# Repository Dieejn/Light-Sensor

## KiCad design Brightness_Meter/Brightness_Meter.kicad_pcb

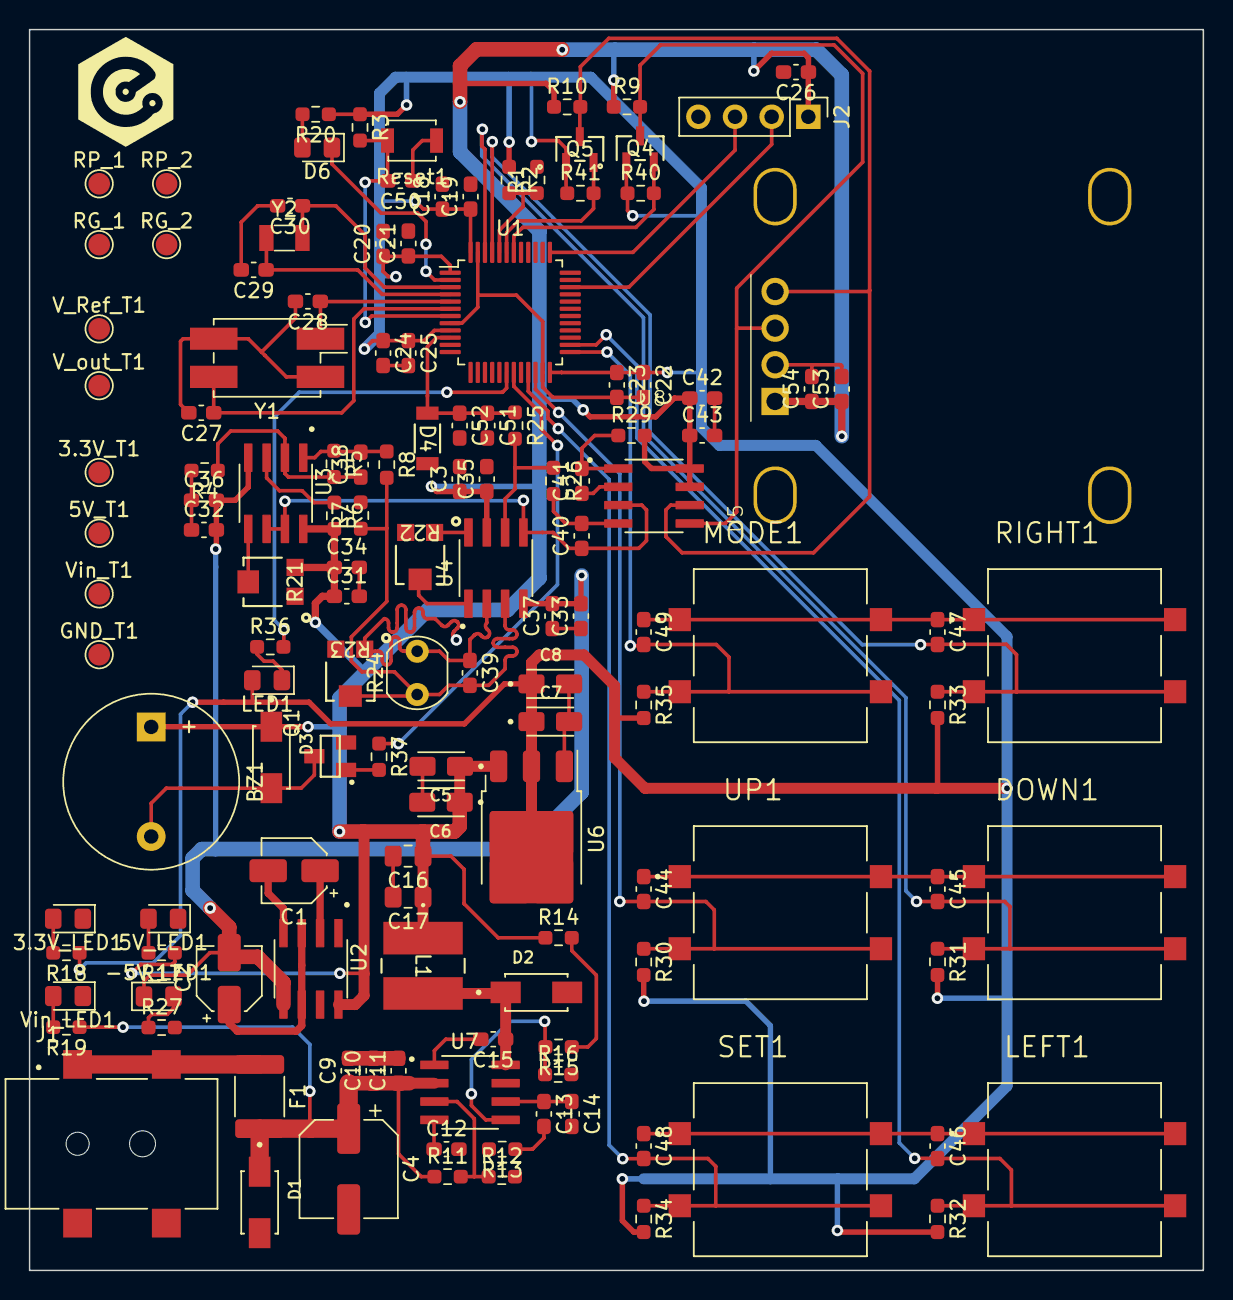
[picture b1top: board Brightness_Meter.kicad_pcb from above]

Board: 2 copper layers, 81.4 x 86.0 mm, 137 parts (0 on the bottom side), 57 nets.

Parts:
3.3V_LED1, 5V_LED1: BLUE; LED_0805_2012Metric_Pad1.15x1.40mm_HandSolder
3.3V_T1: 3.3V; TestPoint_Pad_D1.5mm
5V_T1: 5V; TestPoint_Pad_D1.5mm
-5V_LED1: BLUE; LED_0805_2012Metric_Pad1.15x1.40mm_HandSolder
BZ1: Buzzer; Buzzer_12x9.5RM7.6
C1, C2: 10uF/16V; CP_Elec_4x5.4
C3, C26, C31, C32, C33, C42, C51, C53: 10uF/16V; C_0603_1608Metric_Pad1.08x0.95mm_HandSolder
C4: 22uF/25V; CP_Elec_6.3x5.4
C5, C8: 1uF/25V; CAPMP3216X180N
C6, C7: 10uF/16V; CAPMP3216X180N
C9, C10: 4.7uF/25V; C_0603_1608Metric_Pad1.08x0.95mm_HandSolder
C11, C12, C25: 10nF/50V; C_0603_1608Metric_Pad1.08x0.95mm_HandSolder
C13: 1nF/50V; C_0603_1608Metric_Pad1.08x0.95mm_HandSolder
C14: 47pF/50V; C_0603_1608Metric_Pad1.08x0.95mm_HandSolder
C15: 0.1uF/16V; C_0603_1608Metric_Pad1.08x0.95mm_HandSolder
C16, C17: 47uF/6.3V; C_0805_2012Metric_Pad1.18x1.45mm_HandSolder
C18, C20, C22: 4.7uF/10V; C_0603_1608Metric_Pad1.08x0.95mm_HandSolder
C19, C21, C23, C34, C35, C36, C37, C40, C41, C43, C44, C45, C46, C47, C48, C49, C50, C52, C54: 100nF/16V; C_0603_1608Metric_Pad1.08x0.95mm_HandSolder
C24, C39: 1uF/16V; C_0603_1608Metric_Pad1.08x0.95mm_HandSolder
C27, C28, C29, C30: 20pF/50V; C_0603_1608Metric_Pad1.08x0.95mm_HandSolder
C38: 10pF/50V; C_0603_1608Metric_Pad1.08x0.95mm_HandSolder
D1, D2, D3: SS34; DIOM4325X250N
D4: ZMM3V3; ZDO_ZMM_3p5x1p45_STM
D6: Led_test; LED_0805_2012Metric_Pad1.15x1.40mm_HandSolder
DOWN1: DOWN; SW_TL3300CF260Q
F1: Fuse_Small; Fuse_1812_4532Metric_Pad1.30x3.40mm_HandSolder
GND_T1: GND; TestPoint_Pad_D1.5mm
J1: JACK-DC; SPARKFUN_PRT-12748
J2: Load Program; PinHeader_1x04_P2.54mm_Vertical
L1: 6.8uH/2.2A; IND_SDE0604A_5P8X5P2X4P5_BRN
LED1: RED; LED_0805_2012Metric_Pad1.15x1.40mm_HandSolder
LEFT1: LEFT; SW_TL3300CF260Q
MODE1: MODE; SW_TL3300CF260Q
Q1: MMBT2222A; SOT23
Q4, Q5: BSN20; SOT23_NEX
R1, R2, R25, R26: 0/1%; R_0603_1608Metric_Pad0.98x0.95mm_HandSolder
R3, R9, R10, R16, R30, R31, R32, R33, R34, R35, R40, R41: 10k/1%; R_0603_1608Metric_Pad0.98x0.95mm_HandSolder
R4, R5, R6, R7, R8: R_Small_US; R_0603_1608Metric_Pad0.98x0.95mm_HandSolder
R11: 330k/1%; R_0603_1608Metric_Pad0.98x0.95mm_HandSolder
R12: 47k/1%; R_0603_1608Metric_Pad0.98x0.95mm_HandSolder
R13: 30k/1%; R_0603_1608Metric_Pad0.98x0.95mm_HandSolder
R14: 2.49k/1%; R_0603_1608Metric_Pad0.98x0.95mm_HandSolder
R15: 49.9k/1%; R_0603_1608Metric_Pad0.98x0.95mm_HandSolder
R17, R18, R20, R36, R37: 1k/1%; R_0603_1608Metric_Pad0.98x0.95mm_HandSolder
R19, R27: 4.7k/1%; R_0603_1608Metric_Pad0.98x0.95mm_HandSolder
R21: EVM-3ESX50B14; EVM-3ESX50B14_PAN
R22, R23: EVM-3E; EVM-3ESX50B14_PAN
R24: GL5528; R_LDR_5.0x4.1mm_P3mm_Vertical
R29: 220/1%; R_0603_1608Metric_Pad0.98x0.95mm_HandSolder
RG_1, RG_2: RG; TestPoint_Pad_D1.5mm
RIGHT1: RIGHT; SW_TL3300CF260Q
RP_1, RP_2: RP; TestPoint_Pad_D1.5mm
Reset1: SW_Push; SW_SPST_B3U-1000P
SET1: SET; SW_TL3300CF260Q
U1: STM32F030C8Tx; LQFP-48_7x7mm_P0.5mm
U2: ICL7662CPA; SOIC127P600X175-8N
U3: MCP6002; SOIC127P599X173-8N
U4: INA128; SOIC127P599X175-8N
U5: SSD1306
U6: LM1117DT-3.3; TO-252-3_TabPin2
U7: TPS54331D; SOIC127P599X175-8N
U8: HX710B
UP1: UP; SW_TL3300CF260Q
V_Ref_T1: V_Ref; TestPoint_Pad_D1.5mm
V_out_T1: V_out; TestPoint_Pad_D1.5mm
Vin_LED1: BLUE; LED_0805_2012Metric_Pad1.15x1.40mm_HandSolder
Vin_T1: Vin; TestPoint_Pad_D1.5mm
Y1: 8MHz; Crystal_SMD_EuroQuartz_MQ-4Pin_7.0x5.0mm_HandSoldering
Y2: 32.768KHz; Crystal_SMD_3215-2Pin_3.2x1.5mm

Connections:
+3.3V: 3.3V_T1.1, C7.1, C8.1, C18.1, C19.1, C20.1, C21.1, C22.1, C23.1, C24.1, C25.1, LED1.2 (A), Q4.1 (G), Q5.1 (G), R2.1, R3.1, R18.1, R20.1, R30.2, R31.2, R32.2, R33.2, R34.2, R35.2, R40.1, R41.1, U1.1 (VDD), U1.9 (VDDA), U1.24 (VDD), U1.48 (VDD), U6.2 (VO)
+5V: 5V_T1.1, BZ1.1 (-), C3.1, C5.1, C6.1, C16.1, C17.1, C26.1, C31.1, C34.1, C35.1, C42.1, C43.1, C53.1, C54.1, D3.C, J2.1, L1.1, R6.2, R9.1, R10.1, R14.1, R17.1, R21.3, R29.2, U2.8 (V+), U3.8 (VDD), U4.7 (V+), U5.1 (vcc), U6.3 (VI), U8.7 (DVDD), U8.8 (AVDD)
-5V: -5V_LED1.1 (K), C2.2, C32.2, C33.2, C36.2, C37.2, U2.5 (VOUT), U3.4 (VSS), U4.4 (V-)
/MCU/BOOT0: R1.1, R2.2, U1.44 (BOOT0)
/MCU/LED_TEST: D6.1 (K), U1.2 (PC13)
/MCU/OSC32_IN: C30.1, U1.3 (PC14), Y2.1
/MCU/OSC32_OUT: C29.1, U1.4 (PC15), Y2.2
/MCU/OSC_IN: C28.1, U1.5 (PF0), Y1.1
/MCU/OSC_OUT: C27.1, U1.6 (PF1), Y1.3
/MCU/RESET: C50.2, R3.2, Reset1.2, U1.7 (NRST)
/MCU/SWCLK: J2.3, U1.37 (PA14)
/MCU/SWDIO: J2.2, U1.34 (PA13)
/Power/Vin: C4.1, C9.1, C10.1, C11.1, D1.C, F1.2, R11.1, R19.1, U7.2 (VIN), Vin_T1.1
/measure/CURRENT_SRC: C39.2, R7.1, R8.2, R23.2, R24.1, RP_1.1, U4.3 (+)
/measure/vout: R25.2, R26.1, U4.6, V_out_T1.1
ADC_HX71OB: C40.2, R26.2, U8.4 (INP)
ADC_INO: C51.1, C52.1, D4.1, R25.1, U1.10 (PA0)
BUZZER: R37.1, U1.19 (PB1)
GND: 3.3V_LED1.1 (K), 5V_LED1.1 (K), C2.1, C3.2, C4.2, C5.2, C6.2, C7.2, C8.2, C9.2, C10.2, C11.2, C12.2, C14.2, C16.2, C17.2, C18.2, C19.2, C20.2, C21.2, C22.2, C23.2, C24.2, C25.2, C26.2, C27.2, C28.2, C29.2, C30.2, C31.2, C32.1, C33.1, C34.2, C35.2, C36.1, C37.1, C39.1, C41.1, C42.2, C43.2, C44.1, C45.1, C46.1, C47.1, C48.1, C49.1, C50.1, C51.2, C52.2, C53.2, C54.2, D1.A, D2.A, D4.2, DOWN1.1, DOWN1.2, GND_T1.1, J1.2, J1.3, J2.4, LEFT1.1, LEFT1.2, MODE1.1, MODE1.2, Q1.2, R1.2, R4.2, R12.2, R13.2, R16.2, R21.1, R23.1, R24.2, R27.2, RIGHT1.1, RIGHT1.2, RP_2.1, Reset1.1, SET1.1, SET1.2, U1.8 (VSSA), U1.23 (VSS), U1.47 (VSS), U2.3 (GND), U2.6 (LV), U4.2 (-), U5.2 (gnd), U6.1 (GND), U7.7 (GND), U8.2 (AGND), UP1.1, UP1.2, Vin_LED1.1 (K), Y1.2, Y1.4
I2C_SCL: Q4.2 (S), R40.2, U1.42 (PB6)
I2C_SDA: Q5.2 (S), R41.2, U1.43 (PB7)
LED_INFO: R36.2, U1.18 (PB0)
unnamed: 3.3V_LED1.2 (A), R18.2
unnamed: 5V_LED1.2 (A), R17.2
unnamed: -5V_LED1.2 (A), R27.1
unnamed: BZ1.2 (+), D3.A, Q1.3
unnamed: C13.2, R13.1
unnamed: D6.2 (A), R20.2
unnamed: F1.1, J1.1_1, J1.1_2
unnamed: LED1.1 (K), R36.1
unnamed: Q1.1, R37.2
unnamed: R14.2, R15.1
unnamed: R22.1, RG_2.1, U4.8 (Rg)
unnamed: R22.2, RG_1.1, U4.1 (Rg)
unnamed: C1.1, U2.2 (CAP+)
unnamed: C1.2, U2.4 (CAP-)
unnamed: R6.1, R7.2, U3.3 (VINA+)
unnamed: C38.1, R4.1, R5.2, U3.2 (VINA-)
unnamed: R21.2, U3.5 (VINB+)
unnamed: C38.2, R5.1, R8.1, U3.1 (VOUTA)
unnamed: C15.2, U7.1 (BOOT)
unnamed: C13.1, C14.1, U7.6 (COMP)
unnamed: R11.2, R12.1, U7.3 (EN)
unnamed: C15.1, D2.C, L1.2, U7.8 (PH)
unnamed: C12.1, U7.4 (SS)
unnamed: R15.2, R16.1, U7.5 (VSENSE)
unnamed: C41.2, R29.1, U8.1 (VREF)
unnamed: R19.2, Vin_LED1.2 (A)
SCL_HX710B: Q4.3 (D), R9.2, U5.3 (scl), U8.5 (PD_SCK)
SDA_HX710B: Q5.3 (D), R10.2, U5.4 (sda), U8.6 (DOUT)
SW_DOWN: C45.2, DOWN1.3, DOWN1.4, R31.1, U1.46 (PB9)
SW_LEFT: C46.2, LEFT1.3, LEFT1.4, R32.1, U1.26 (PB13)
SW_MODE: C49.2, MODE1.3, MODE1.4, R35.1, U1.25 (PB12)
SW_RIGHT: C47.2, R33.1, RIGHT1.3, RIGHT1.4, U1.45 (PB8)
SW_SET: C48.2, R34.1, SET1.3, SET1.4, U1.21 (PB10)
SW_UP: C44.2, R30.1, U1.22 (PB11), UP1.3, UP1.4
VREF: C40.1, U3.6 (VINB-), U3.7 (VOUTB), U4.5 (Ref), U8.3 (INN), V_Ref_T1.1

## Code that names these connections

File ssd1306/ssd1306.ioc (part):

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Mcu.Name=STM32F103C(8-B)Tx
Mcu.Package=LQFP48
Mcu.UserName=STM32F103C8Tx
PA0-WKUP.Signal=ADCx_IN0
PA1.GPIOParameters=GPIO_PuPd,GPIO_Label
PA1.GPIO_Label=SW_LEFT
PA1.GPIO_PuPd=GPIO_PULLUP
PA1.Signal=GPIO_Input
PA10.GPIOParameters=GPIO_Label
PA10.GPIO_Label=BUZZER
PA10.Signal=GPIO_Output
PA13.Mode=Serial_Wire
PA13.Signal=SYS_JTMS-SWDIO
PA14.Mode=Serial_Wire
PA14.Signal=SYS_JTCK-SWCLK
PA2.GPIOParameters=GPIO_PuPd,GPIO_Label
PA2.GPIO_Label=SW_MODE
PA2.GPIO_PuPd=GPIO_PULLUP
PA2.Signal=GPIO_Input
PA3.GPIOParameters=GPIO_PuPd,GPIO_Label
PA3.GPIO_Label=SW_DOWN
PA3.GPIO_PuPd=GPIO_PULLUP
PA3.Signal=GPIO_Input
PA4.GPIOParameters=GPIO_PuPd,GPIO_Label
PA4.GPIO_Label=SW_UP
PA4.GPIO_PuPd=GPIO_PULLUP
PA4.Signal=GPIO_Input
PA5.GPIOParameters=GPIO_PuPd,GPIO_Label
PA5.GPIO_Label=SW_RIGHT
PA5.GPIO_PuPd=GPIO_PULLUP
PA5.Signal=GPIO_Input
PA6.GPIOParameters=GPIO_PuPd,GPIO_Label
PA6.GPIO_Label=SW_SET
PA6.GPIO_PuPd=GPIO_PULLUP
PA6.Signal=GPIO_Input
PA7.GPIOParameters=GPIO_Label
PA7.GPIO_Label=CHANGE_RESISTOR
PA7.Signal=GPIO_Output
PB15.GPIOParameters=GPIO_Label
PB15.GPIO_Label=LED_INFOR
PB15.Signal=GPIO_Output
PB6.Mode=I2C
PB6.Signal=I2C1_SCL
PB7.Mode=I2C
PB7.Signal=I2C1_SDA
PD0-OSC_IN.Mode=HSE-External-Oscillator
PD0-OSC_IN.Signal=RCC_OSC_IN
PD1-OSC_OUT.Mode=HSE-External-Oscillator
PD1-OSC_OUT.Signal=RCC_OSC_OUT
board=custom

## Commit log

2024-05-18 software
2024-05-18 hardware
